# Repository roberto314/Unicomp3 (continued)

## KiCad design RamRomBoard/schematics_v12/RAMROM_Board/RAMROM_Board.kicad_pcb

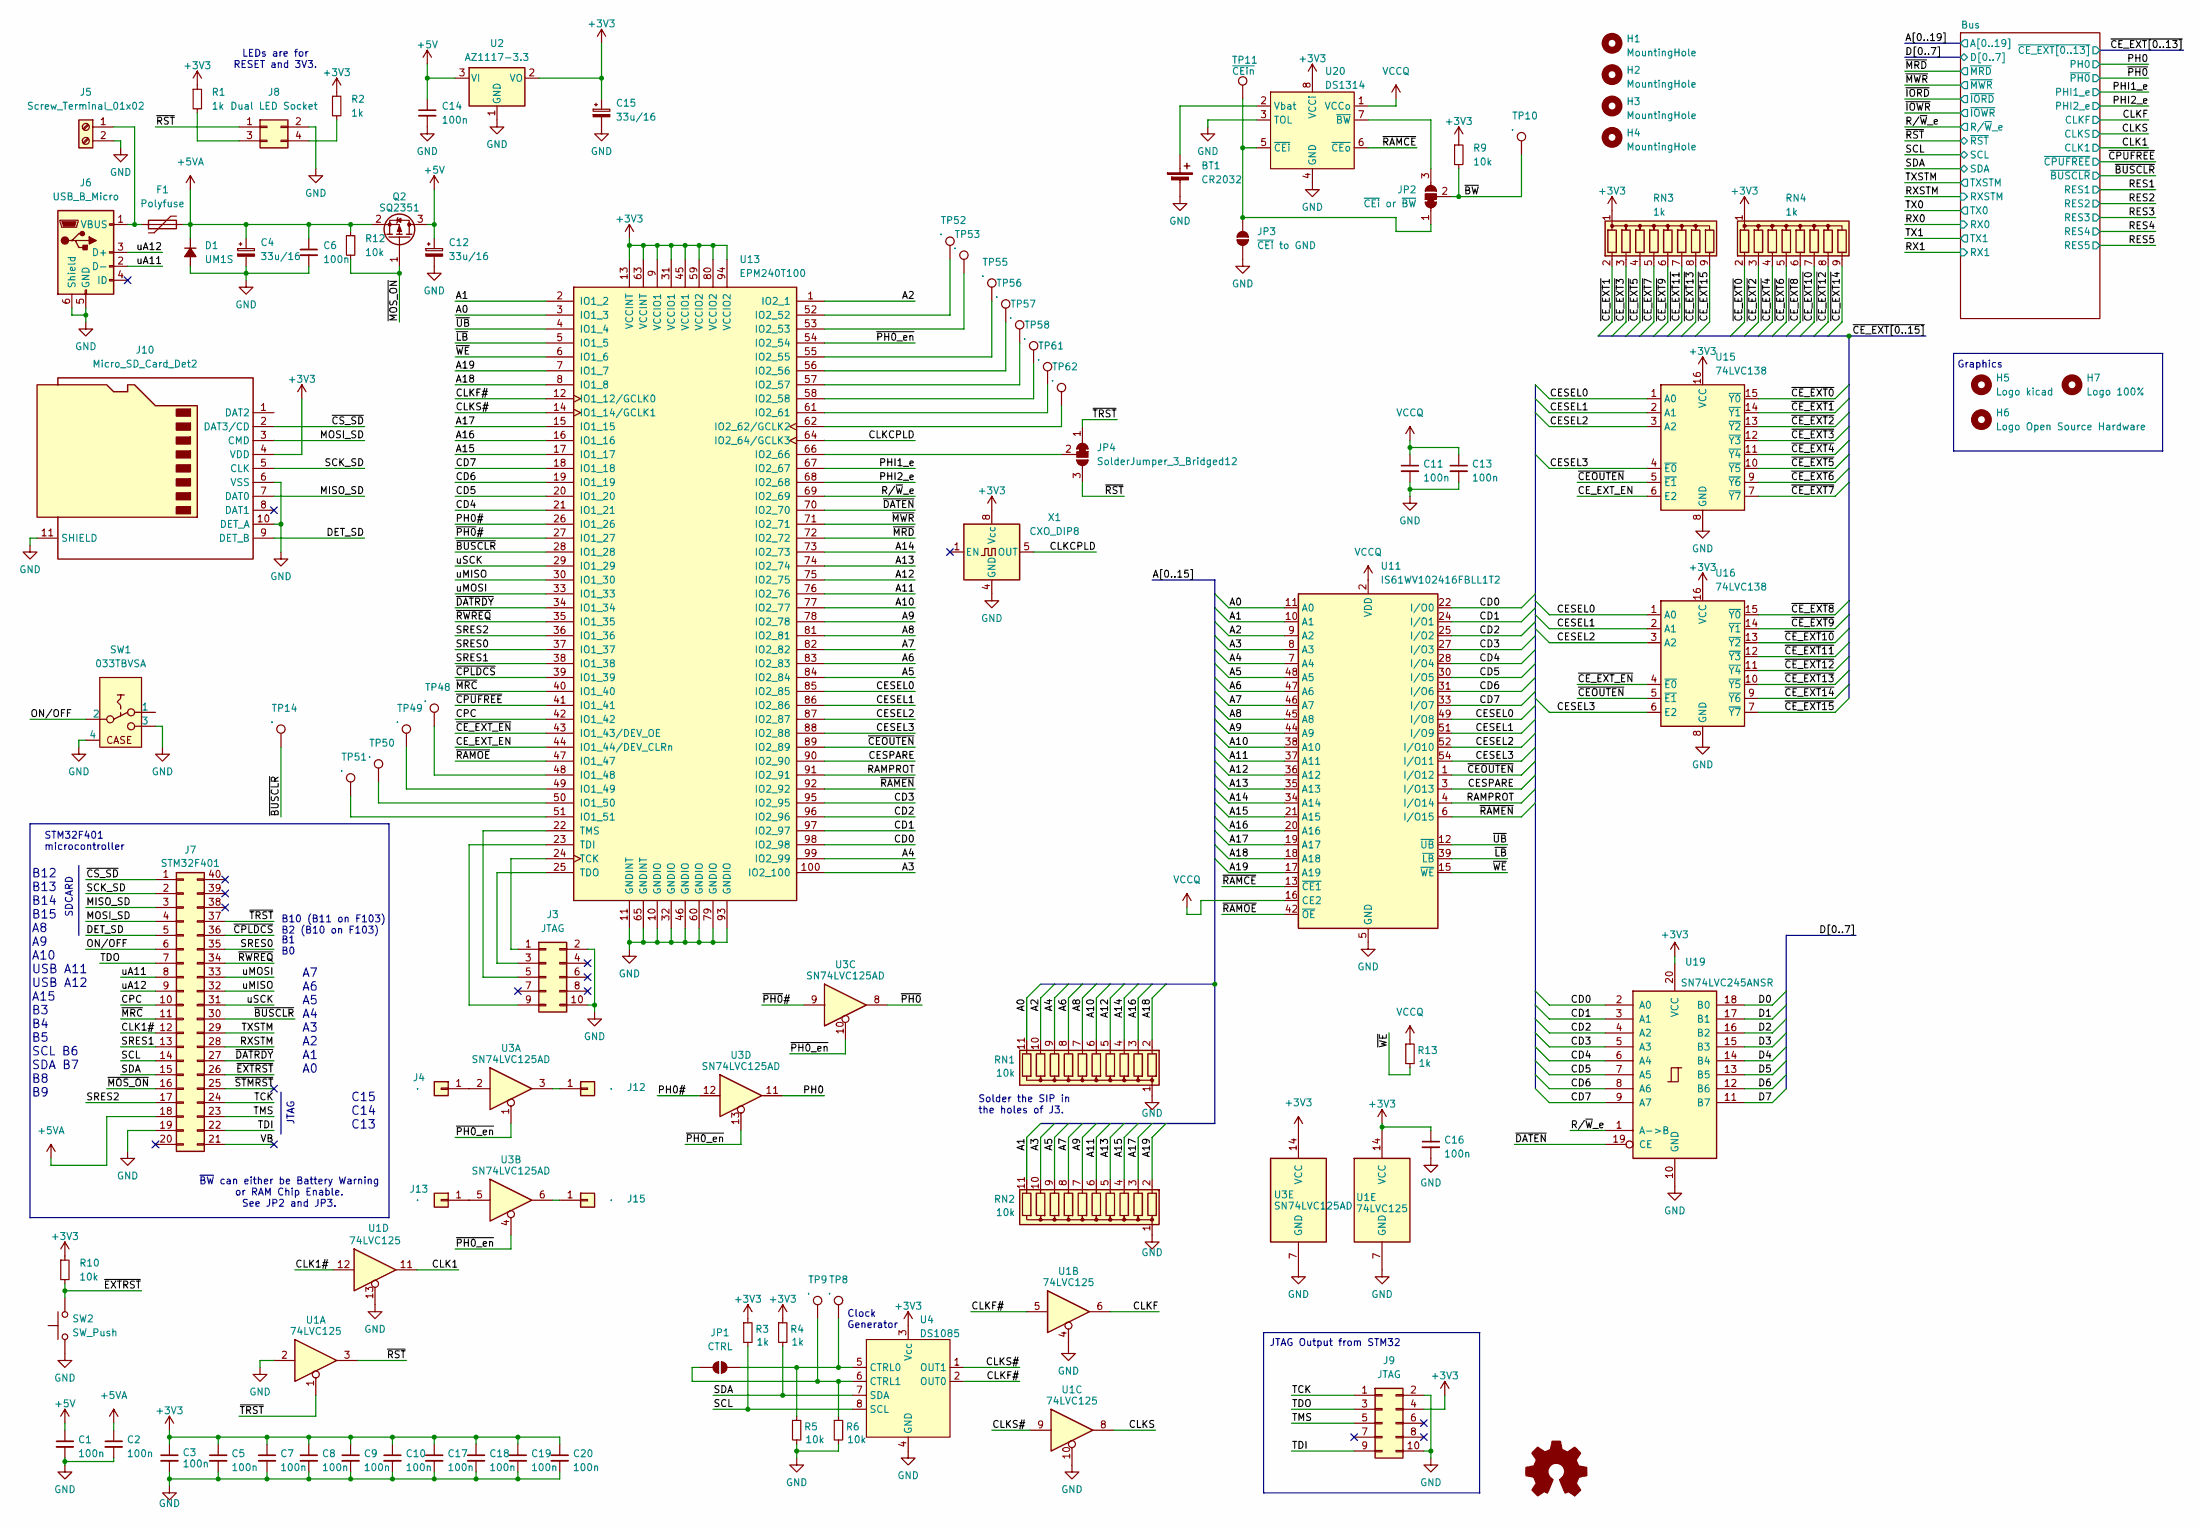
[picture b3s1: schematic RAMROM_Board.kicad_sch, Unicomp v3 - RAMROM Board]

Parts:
BT1: CR2032; Battery_CR2032_Horizontal_ThreeHoles
C1, C2, C3, C5, C6, C7, C8, C9, C10, C11, C13, C14, C16, C17, C18, C19, C20: 100n; C_1206_3216Metric
C4, C12, C15: 33u/16; CP_EIA-7343-31_Kemet-D
D1: UM1S; D_SMB
F1: Polyfuse; Fuse_Littelfuse_395Series
H1, H2, H3, H4: MountingHole; MountingHole_3.2mm_M3
H5: Logo kicad; KiCad-Logo2_6mm_SilkScreen
H6: Logo Open Source Hardware; OSHW-Logo2_7.3x6mm_SilkScreen
H7: Logo 100%; Logo_100ProzentOffner_10x2.7mm
J3: JTAG; PinHeader_2x05_P2.54mm_Vertical
J4, J12, J13, J15: .; PinHeader_1x01_P1.27mm_Vertical
J5: Screw_Terminal_01x02; TerminalBlock_RND_205-00012_1x02_P5.00mm_Horizontal
J6: USB_B_Micro; USB_Micro-B_Amphenol_10104110_Horizontal
J7: STM32F401; DIP-40_W15.24mm_Socket_LongPads
J8: Dual LED Socket; PinHeader_2x02_P2.54mm_Vertical
J9: JTAG; PinHeader_2x05_P2.54mm_Horizontal
J10: Micro_SD_Card_Det2; microSD_HC_Hirose_DM3D-SF
JP1: CTRL; SolderJumper-2_P1.3mm_Open_RoundedPad1.0x1.5mm
JP2: ~{CEi} or ~{BW}; SolderJumper-3_P1.3mm_Bridged12_RoundedPad1.0x1.5mm
JP3: ~{CEi} to GND; SolderJumper-2_P1.3mm_Open_RoundedPad1.0x1.5mm
JP4: SolderJumper_3_Bridged12; SolderJumper-3_P1.3mm_Bridged12_RoundedPad1.0x1.5mm
Q2: SQ2351; SOT-23_Handsoldering
R1, R2, R3, R4, R13: 1k; R_1206_3216Metric
R5, R6, R9, R10, R12: 10k; R_1206_3216Metric
RN1, RN2: 10k; R_Array_SIP11
RN3, RN4: 1k; R_Array_SIP9
SW1: 033TBVSA; ToggleSwitch_CTS_033TBVS
SW2: SW_Push; SW_Tactile_SPST_Angled_PTS645Vx31-2LFS
TP8, TP9, TP10, TP14, TP48, TP49, TP50, TP51, TP52, TP53, TP55, TP56, TP57, TP58, TP61, TP62: .; PinHeader_1x01_P1.00mm_Vertical
TP11: ~{CEin}; PinHeader_1x01_P1.00mm_Vertical
U1: 74LVC125; SOIC-14_3.9x8.7mm_P1.27mm
U2: AZ1117-3.3; SOT-223-3_TabPin2
U3: SN74LVC125AD; SOIC-14_3.9x8.7mm_P1.27mm
U4: DS1085; SOIC-8_3.9x4.9mm_P1.27mm
U11: IS61WV102416FBLL1T2; TSOP-II-54_22.2x10.16mm_P0.8mm
U13: EPM240T100; LQFP-100_14x14mm_P0.5mm
U15, U16: 74LVC138; SOIC-16_3.9x9.9mm_P1.27mm
U19: SN74LVC245ANSR; SO-20_5.3x12.6mm_P1.27mm
U20: DS1314; SOIC-8_3.9x4.9mm_P1.27mm
X1: CXO_DIP8; Oscillator_DIP-8

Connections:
+3V3: C3.1, C5.1, C7.1, C8.1, C9.1, C10.1, C15.1, C16.1, C17.1, C18.1, C19.1, C20.1, J9.4, J10.4 (VDD), R1.1, R2.1, R3.1, R4.1, R9.1, R10.1, RN3.1 (common), RN4.1 (common), U1.14 (VCC), U2.2 (VO), U3.14 (VCC), U4.3 (Vcc), U13.9 (VCCIO1), U13.13 (VCCINT), U13.31 (VCCIO1), U13.45 (VCCIO1), U13.59 (VCCIO2), U13.63 (VCCINT), U13.80 (VCCIO2), U13.94 (VCCIO2), U15.16 (VCC), U16.16 (VCC), U19.20 (VCC), U20.8 (VCCi), X1.8 (Vcc); also elsewhere on the board
+5V: C1.1, C12.1, C14.1, Q2.3 (D), U2.3 (VI); also elsewhere on the board
+5VA: C2.1, C4.1, C6.1, D1.1 (K), F1.2, J7.18, Q2.2 (S), R12.1; also elsewhere on the board
/A0: RN1.11 (R10), U11.11 (A0), U13.3 (IO1_3); also elsewhere on the board
/A1: RN2.11 (R10), U11.10 (A1), U13.2 (IO1_2); also elsewhere on the board
/A2: RN1.10 (R9), U11.9 (A2), U13.1 (IO2_1); also elsewhere on the board
/A3: RN2.10 (R9), U11.8 (A3), U13.100 (IO2_100); also elsewhere on the board
/A4: RN1.9 (R8), U11.7 (A4), U13.99 (IO2_99); also elsewhere on the board
/A5: RN2.9 (R8), U11.48 (A5), U13.84 (IO2_84); also elsewhere on the board
/A6: RN1.8 (R7), U11.47 (A6), U13.83 (IO2_83); also elsewhere on the board
/A7: RN2.8 (R7), U11.46 (A7), U13.82 (IO2_82); also elsewhere on the board
/A8: RN1.7 (R6), U11.45 (A8), U13.81 (IO2_81); also elsewhere on the board
/A9: RN2.7 (R6), U11.44 (A9), U13.78 (IO2_78); also elsewhere on the board
/A10: RN1.6 (R5), U11.38 (A10), U13.77 (IO2_77); also elsewhere on the board
/A11: RN2.6 (R5), U11.37 (A11), U13.76 (IO2_76); also elsewhere on the board
/A12: RN1.5 (R4), U11.36 (A12), U13.75 (IO2_75); also elsewhere on the board
/A13: RN2.5 (R4), U11.35 (A13), U13.74 (IO2_74); also elsewhere on the board
/A14: RN1.4 (R3), U11.34 (A14), U13.73 (IO2_73); also elsewhere on the board
/A15: RN2.4 (R3), U11.21 (A15), U13.17 (IO1_17); also elsewhere on the board
/A16: RN1.3 (R2), U11.20 (A16), U13.16 (IO1_16); also elsewhere on the board
/A17: RN2.3 (R2), U11.19 (A17), U13.15 (IO1_15); also elsewhere on the board
/A18: RN1.2 (R1), U11.18 (A18), U13.8 (IO1_8); also elsewhere on the board
/A19: RN2.2 (R1), U11.17 (A19), U13.7 (IO1_7); also elsewhere on the board
/CD0: U11.22 (I/O0), U13.98 (IO2_98), U19.2 (A0)
/CD1: U11.24 (I/O1), U13.97 (IO2_97), U19.3 (A1)
/CD2: U11.25 (I/O2), U13.96 (IO2_96), U19.4 (A2)
/CD3: U11.27 (I/O3), U13.95 (IO2_95), U19.5 (A3)
/CD4: U11.28 (I/O4), U13.21 (IO1_21), U19.6 (A4)
/CD5: U11.30 (I/O5), U13.20 (IO1_20), U19.7 (A5)
/CD6: U11.31 (I/O6), U13.19 (IO1_19), U19.8 (A6)
/CD7: U11.33 (I/O7), U13.18 (IO1_18), U19.9 (A7)
/CESEL0: U11.49 (I/O8), U13.85 (IO2_85), U15.1 (A0), U16.1 (A0)
/CESEL1: U11.51 (I/O9), U13.86 (IO2_86), U15.2 (A1), U16.2 (A1)
/CESEL2: U11.52 (I/O10), U13.87 (IO2_87), U15.3 (A2), U16.3 (A2)
/CESEL3: U11.54 (I/O11), U13.88 (IO2_88), U15.4 (~E0), U16.6 (E2)
/CESPARE: U11.3 (I/O13), U13.90 (IO2_90)
/CE_EXT_EN: U13.44 (IO1_44/DEV_CLRn), U15.6 (E2)
/CLK1: U1.11; also elsewhere on the board
/CLK1#: J7.12, U1.12
/CLKCPLD: U13.64 (IO2_64/GCLK3), X1.5 (OUT)
/CLKF: U1.6; also elsewhere on the board
/CLKF#: U1.5, U4.2 (OUT0), U13.12 (IO1_12/GCLK0)
/CLKS: U1.8; also elsewhere on the board
/CLKS#: U1.9, U4.1 (OUT1), U13.14 (IO1_14/GCLK1)
/CPC: J7.10, U13.42 (IO1_42)
/D0: U19.18 (B0); also elsewhere on the board
/D1: U19.17 (B1); also elsewhere on the board
/D2: U19.16 (B2); also elsewhere on the board
/D3: U19.15 (B3); also elsewhere on the board
/D4: U19.14 (B4); also elsewhere on the board
/D5: U19.13 (B5); also elsewhere on the board
/D6: U19.12 (B6); also elsewhere on the board
/D7: U19.11 (B7); also elsewhere on the board
/DET_SD: J7.5, J10.9 (DET_B)
/MISO_SD: J7.3, J10.7 (DAT0)
/MOSI_SD: J7.4, J10.3 (CMD)
/ON/OFF: J7.6, SW1.2
/PH0: U3.11; also elsewhere on the board
/PH0#: U3.12, U13.26 (IO1_26)
/PHI1_e: U13.67 (IO2_67); also elsewhere on the board
/PHI2_e: U13.68 (IO2_68); also elsewhere on the board
/RAMPROT: U11.4 (I/O14), U13.91 (IO2_91)
/RXSTM: J7.28; also elsewhere on the board
/R/~W_e: U13.69 (IO2_69), U19.1 (A->B); also elsewhere on the board
/SCK_SD: J7.2, J10.5 (CLK)
/SCL: J7.14, R3.2, U4.8 (SCL); also elsewhere on the board
/SDA: J7.15, R4.2, U4.7 (SDA); also elsewhere on the board
/SRES0: J7.35, U13.37 (IO1_37)
/SRES1: J7.13, U13.38 (IO1_38)
/SRES2: J7.17, U13.36 (IO1_36)
/TCK: J7.24, J9.1
/TDI: J7.22, J9.9
/TDO: J7.7, J9.3
/TMS: J7.23, J9.5
/TXSTM: J7.29; also elsewhere on the board
/VB: J7.21
/uA11: J6.2 (D-), J7.8
/uA12: J6.3 (D+), J7.9
/uMISO: J7.32, U13.30 (IO1_30)
/uMOSI: J7.33, U13.33 (IO1_33)
/uSCK: J7.31, U13.29 (IO1_29)
/~BUSCLR: J7.30, TP14.1, U13.28 (IO1_28); also elsewhere on the board
/~BW: JP2.2 (C), R9.2, TP10.1
/~CEOUTEN: U11.1 (I/O12), U13.89 (IO2_89), U15.5 (~E1), U16.5 (~E1)
/~CE_EXT0: RN4.2 (R1), U15.15 (~Y0); also elsewhere on the board
/~CE_EXT1: RN3.2 (R1), U15.14 (~Y1); also elsewhere on the board
/~CE_EXT2: RN4.3 (R2), U15.13 (~Y2); also elsewhere on the board
/~CE_EXT3: RN3.3 (R2), U15.12 (~Y3); also elsewhere on the board
/~CE_EXT4: RN4.4 (R3), U15.11 (~Y4); also elsewhere on the board
/~CE_EXT5: RN3.4 (R3), U15.10 (~Y5); also elsewhere on the board
/~CE_EXT6: RN4.5 (R4), U15.9 (~Y6); also elsewhere on the board
/~CE_EXT7: RN3.5 (R4), U15.7 (~Y7); also elsewhere on the board
/~CE_EXT8: RN4.6 (R5), U16.15 (~Y0); also elsewhere on the board
/~CE_EXT9: RN3.6 (R5), U16.14 (~Y1); also elsewhere on the board
/~CE_EXT10: RN4.7 (R6), U16.13 (~Y2); also elsewhere on the board
/~CE_EXT11: RN3.7 (R6), U16.12 (~Y3); also elsewhere on the board
/~CE_EXT12: RN4.8 (R7), U16.11 (~Y4); also elsewhere on the board
/~CE_EXT13: RN3.8 (R7), U16.10 (~Y5); also elsewhere on the board
/~CE_EXT14: RN4.9 (R8), U16.9 (~Y6)
/~CE_EXT15: RN3.9 (R8), U16.7 (~Y7)
/~CE_EXT_EN: U13.43 (IO1_43/DEV_OE), U16.4 (~E0)
/~CPLDCS: J7.36, U13.39 (IO1_39)
/~CPUFREE: U13.41 (IO1_41); also elsewhere on the board
/~CS_SD: J7.1, J10.2 (DAT3/CD)
/~DATEN: U13.70 (IO2_70), U19.19 (CE)
/~DATRDY: J7.27, U13.34 (IO1_34)
/~EXTRST: J7.26, R10.2, SW2.2
/~LB: U11.39 (~LB), U13.5 (IO1_5)
/~MOS_ON: J7.16, Q2.1 (G), R12.2
/~MRC: J7.11, U13.40 (IO1_40)
/~MRD: U13.72 (IO2_72); also elsewhere on the board
/~MWR: U13.71 (IO2_71); also elsewhere on the board
/~PH0_en: U3.1, U3.4, U3.10, U3.13, U13.54 (IO2_54)
/~PH0: U3.8; also elsewhere on the board
/~PH0#: U3.9, U13.27 (IO1_27)
/~RAMCE: U11.13 (~CE1), U20.6 (~CEo)
/~RAMEN: U11.6 (I/O15), U13.92 (IO2_92)
/~RAMOE: U11.42 (~OE), U13.47 (IO1_47)
/~RST: J8.1, JP4.3 (B), U1.3; also elsewhere on the board
/~RWREQ: J7.34, U13.35 (IO1_35)
/~STMRST: J7.25
/~TRST: J7.37, JP4.1 (A), U1.1
/~UB: U11.12 (~UB), U13.4 (IO1_4)
/~WE: R13.2, U11.15 (~WE), U13.6 (IO1_6)
GND: BT1.2 (-), C1.2, C2.2, C3.2, C4.2, C5.2, C6.2, C7.2, C8.2, C9.2, C10.2, C11.2, C12.2, C13.2, C14.2, C15.2, C16.2, C17.2, C18.2, C19.2, C20.2, D1.2 (A), J3.2, J3.10, J5.2, J6.5 (GND), J6.6 (Shield), J7.19, J8.2, J9.2, J9.10, J10.6 (VSS), J10.10 (DET_A), J10.11 (SHIELD), JP3.1 (A), R5.2, R6.2, RN1.1 (common), RN2.1 (common), SW1.3, SW1.4, SW2.1, U1.2, U1.4, U1.7 (GND), U1.10, U1.13, U2.1 (GND), U3.7 (GND), U4.4 (GND), U11.5 (GND), U11.26 (GND), U11.32 (GND), U11.41 (GND), U11.53 (GND), U13.10 (GNDIO), U13.11 (GNDINT), U13.32 (GNDIO), U13.46 (GNDIO), U13.60 (GNDIO), U13.65 (GNDINT), U13.79 (GNDIO), U13.93 (GNDIO), U15.8 (GND), U16.8 (GND), U19.10 (GND), U20.3 (TOL), U20.4 (GND), X1.4 (GND); also elsewhere on the board
unnamed: BT1.1 (+), U20.2 (Vbat)
unnamed: J3.1, U13.24 (TCK)
unnamed: J3.3, U13.25 (TDO)
unnamed: J3.5, U13.22 (TMS)
unnamed: J3.9, U13.23 (TDI)
unnamed: J4.1, U3.2
unnamed: F1.1, J5.1, J6.1 (VBUS)
unnamed: J8.3, R1.2
unnamed: J8.4, R2.2
unnamed: J12.1, U3.3
unnamed: J13.1, U3.5
unnamed: J15.1, U3.6
unnamed: JP1.1 (A), R5.1, TP8.1, U4.5 (CTRL0)
unnamed: JP1.2 (B), R6.1, TP9.1, U4.6 (CTRL1)
unnamed: JP2.1 (A), JP3.2 (B), TP11.1, U20.5 (~CEi)
unnamed: JP2.3 (B), U20.7 (~BW)
unnamed: JP4.2 (C), U13.66 (IO2_66)
unnamed: TP48.1, U13.48 (IO1_48)
unnamed: TP49.1, U13.49 (IO1_49)
unnamed: TP50.1, U13.50 (IO1_50)
unnamed: TP51.1, U13.51 (IO1_51)
unnamed: TP52.1, U13.52 (IO2_52)
unnamed: TP53.1, U13.53 (IO2_53)
unnamed: TP55.1, U13.55 (IO2_55)
unnamed: TP56.1, U13.56 (IO2_56)
unnamed: TP57.1, U13.57 (IO2_57)
unnamed: TP58.1, U13.58 (IO2_58)
unnamed: TP61.1, U13.61 (IO2_61)
unnamed: TP62.1, U13.62 (IO2_62/GCLK2)
VCCQ: C11.1, C13.1, R13.1, U11.2 (VDD), U11.14 (VDD), U11.16 (CE2), U11.23 (VDD), U11.29 (VDD), U11.50 (VDD), U20.1 (VCCo)

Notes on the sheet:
JTAG Output from STM32
SDCARD
B1 B0
JTAG
Graphics
LEDs are for RESET and 3V3.
~{BW} can either be Battery Warning or RAM Chip Enable. See JP2 and JP3.
B10 (B11 on F103) B2 (B10 on F103)
A7 A6 A5 A4 A3 A2 A1 A0
Clock Generator
Solder the SIP in the holes of J3.
B12 B13 B14 B15 A8 A9 A10 USB A11 USB A12 A15 B3 B4 B5 SCL B6 SDA B7 B8 B9
C15 C14 C13
STM32F401 microcontroller

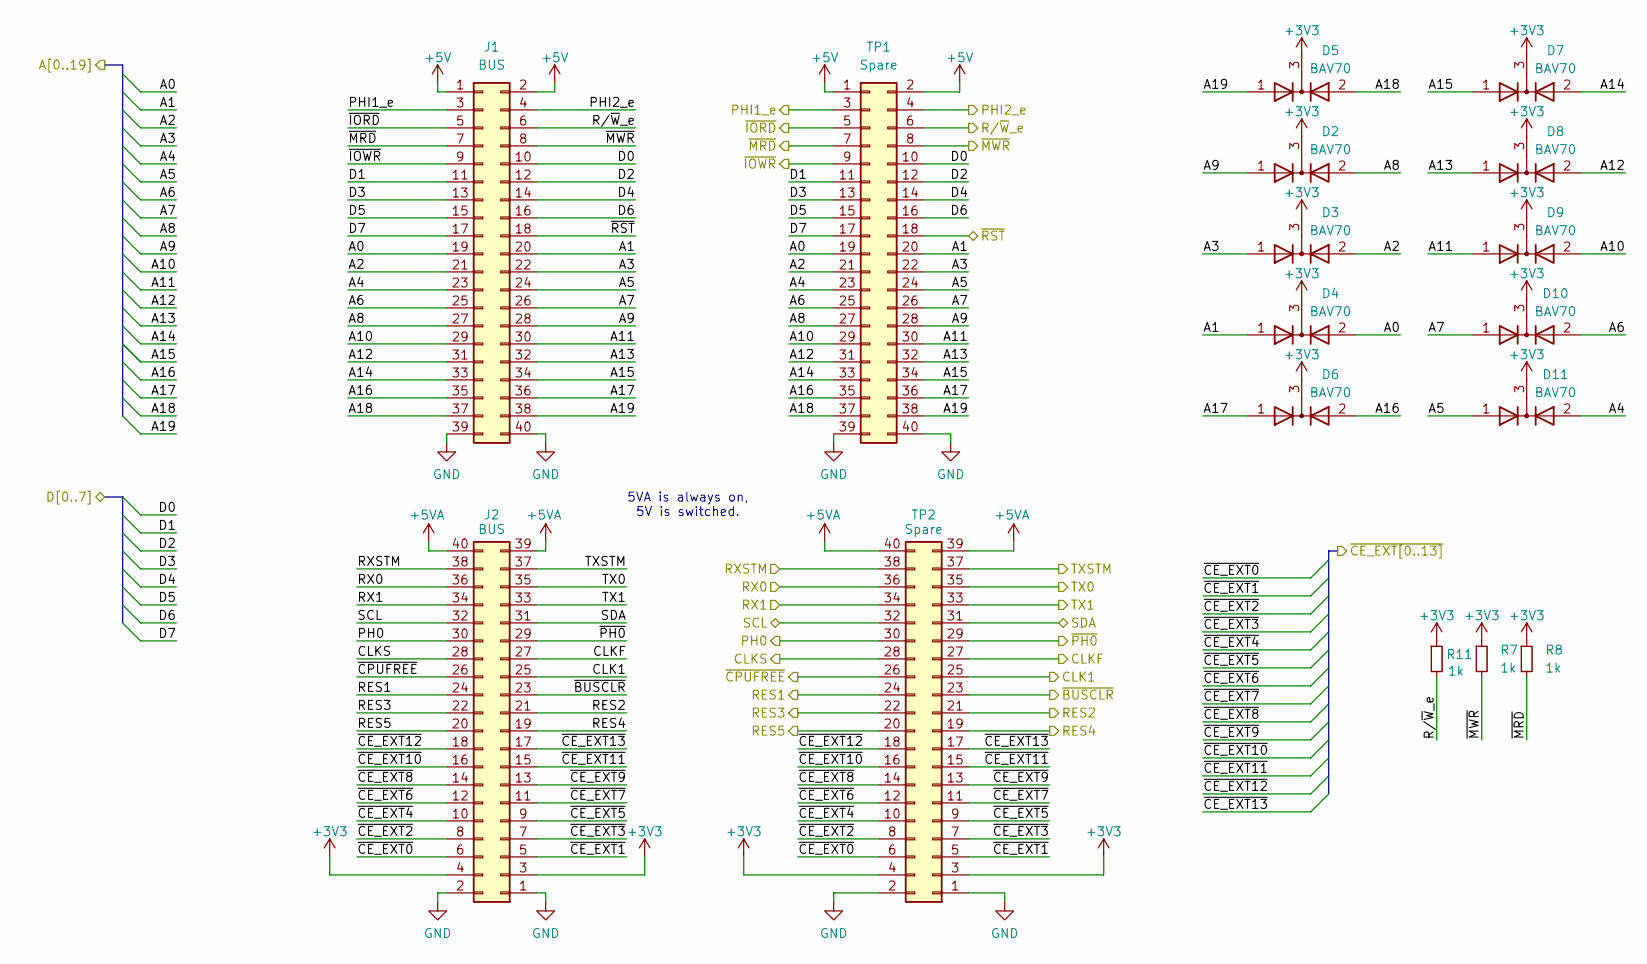
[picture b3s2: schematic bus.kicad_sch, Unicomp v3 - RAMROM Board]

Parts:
D2, D3, D4, D5, D6, D7, D8, D9, D10, D11: BAV70; SOT-23
J1, J2: BUS; PinSocket_2x20_P2.54mm_Vertical
R7, R8, R11: 1k; R_1206_3216Metric
TP1, TP2: Spare; PinSocket_2x20_P2.54mm_Vertical

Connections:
+3V3: D2.3 (K), D3.3 (K), D4.3 (K), D5.3 (K), D6.3 (K), D7.3 (K), D8.3 (K), D9.3 (K), D10.3 (K), D11.3 (K), J2.3, J2.4, R7.1, R8.1, R11.1, TP2.3, TP2.4; also elsewhere on the board
+5V: J1.1, J1.2, TP1.1, TP1.2; also elsewhere on the board
+5VA: J2.39, J2.40, TP2.39, TP2.40; also elsewhere on the board
/A0: D4.2 (A), J1.19, TP1.19; also elsewhere on the board
/A1: D4.1 (A), J1.20, TP1.20; also elsewhere on the board
/A2: D3.2 (A), J1.21, TP1.21; also elsewhere on the board
/A3: D3.1 (A), J1.22, TP1.22; also elsewhere on the board
/A4: D11.2 (A), J1.23, TP1.23; also elsewhere on the board
/A5: D11.1 (A), J1.24, TP1.24; also elsewhere on the board
/A6: D10.2 (A), J1.25, TP1.25; also elsewhere on the board
/A7: D10.1 (A), J1.26, TP1.26; also elsewhere on the board
/A8: D2.2 (A), J1.27, TP1.27; also elsewhere on the board
/A9: D2.1 (A), J1.28, TP1.28; also elsewhere on the board
/A10: D9.2 (A), J1.29, TP1.29; also elsewhere on the board
/A11: D9.1 (A), J1.30, TP1.30; also elsewhere on the board
/A12: D8.2 (A), J1.31, TP1.31; also elsewhere on the board
/A13: D8.1 (A), J1.32, TP1.32; also elsewhere on the board
/A14: D7.2 (A), J1.33, TP1.33; also elsewhere on the board
/A15: D7.1 (A), J1.34, TP1.34; also elsewhere on the board
/A16: D6.2 (A), J1.35, TP1.35; also elsewhere on the board
/A17: D6.1 (A), J1.36, TP1.36; also elsewhere on the board
/A18: D5.2 (A), J1.37, TP1.37; also elsewhere on the board
/A19: D5.1 (A), J1.38, TP1.38; also elsewhere on the board
/CLK1: J2.25, TP2.25; also elsewhere on the board
/CLKF: J2.27, TP2.27; also elsewhere on the board
/CLKS: J2.28, TP2.28; also elsewhere on the board
/D0: J1.10, TP1.10; also elsewhere on the board
/D1: J1.11, TP1.11; also elsewhere on the board
/D2: J1.12, TP1.12; also elsewhere on the board
/D3: J1.13, TP1.13; also elsewhere on the board
/D4: J1.14, TP1.14; also elsewhere on the board
/D5: J1.15, TP1.15; also elsewhere on the board
/D6: J1.16, TP1.16; also elsewhere on the board
/D7: J1.17, TP1.17; also elsewhere on the board
/PH0: J2.30, TP2.30; also elsewhere on the board
/PHI1_e: J1.3, TP1.3; also elsewhere on the board
/PHI2_e: J1.4, TP1.4; also elsewhere on the board
/RES1: J2.24, TP2.24
/RES2: J2.21, TP2.21
/RES3: J2.22, TP2.22
/RES4: J2.19, TP2.19
/RES5: J2.20, TP2.20
/RX0: J2.36, TP2.36
/RX1: J2.34, TP2.34
/RXSTM: J2.38, TP2.38; also elsewhere on the board
/R/~W_e: J1.6, R11.2, TP1.6; also elsewhere on the board
/SCL: J2.32, TP2.32; also elsewhere on the board
/SDA: J2.31, TP2.31; also elsewhere on the board
/TX0: J2.35, TP2.35
/TX1: J2.33, TP2.33
/TXSTM: J2.37, TP2.37; also elsewhere on the board
/~BUSCLR: J2.23, TP2.23; also elsewhere on the board
/~CE_EXT0: J2.6, TP2.6; also elsewhere on the board
/~CE_EXT1: J2.5, TP2.5; also elsewhere on the board
/~CE_EXT2: J2.8, TP2.8; also elsewhere on the board
/~CE_EXT3: J2.7, TP2.7; also elsewhere on the board
/~CE_EXT4: J2.10, TP2.10; also elsewhere on the board
/~CE_EXT5: J2.9, TP2.9; also elsewhere on the board
/~CE_EXT6: J2.12, TP2.12; also elsewhere on the board
/~CE_EXT7: J2.11, TP2.11; also elsewhere on the board
/~CE_EXT8: J2.14, TP2.14; also elsewhere on the board
/~CE_EXT9: J2.13, TP2.13; also elsewhere on the board
/~CE_EXT10: J2.16, TP2.16; also elsewhere on the board
/~CE_EXT11: J2.15, TP2.15; also elsewhere on the board
/~CE_EXT12: J2.18, TP2.18; also elsewhere on the board
/~CE_EXT13: J2.17, TP2.17; also elsewhere on the board
/~CPUFREE: J2.26, TP2.26; also elsewhere on the board
/~IORD: J1.5, TP1.5
/~IOWR: J1.9, TP1.9
/~MRD: J1.7, R8.2, TP1.7; also elsewhere on the board
/~MWR: J1.8, R7.2, TP1.8; also elsewhere on the board
/~PH0: J2.29, TP2.29; also elsewhere on the board
/~RST: J1.18, TP1.18; also elsewhere on the board
GND: J1.39, J1.40, J2.1, J2.2, TP1.39, TP1.40, TP2.1, TP2.2; also elsewhere on the board

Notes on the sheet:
5VA is always on, 5V is switched.

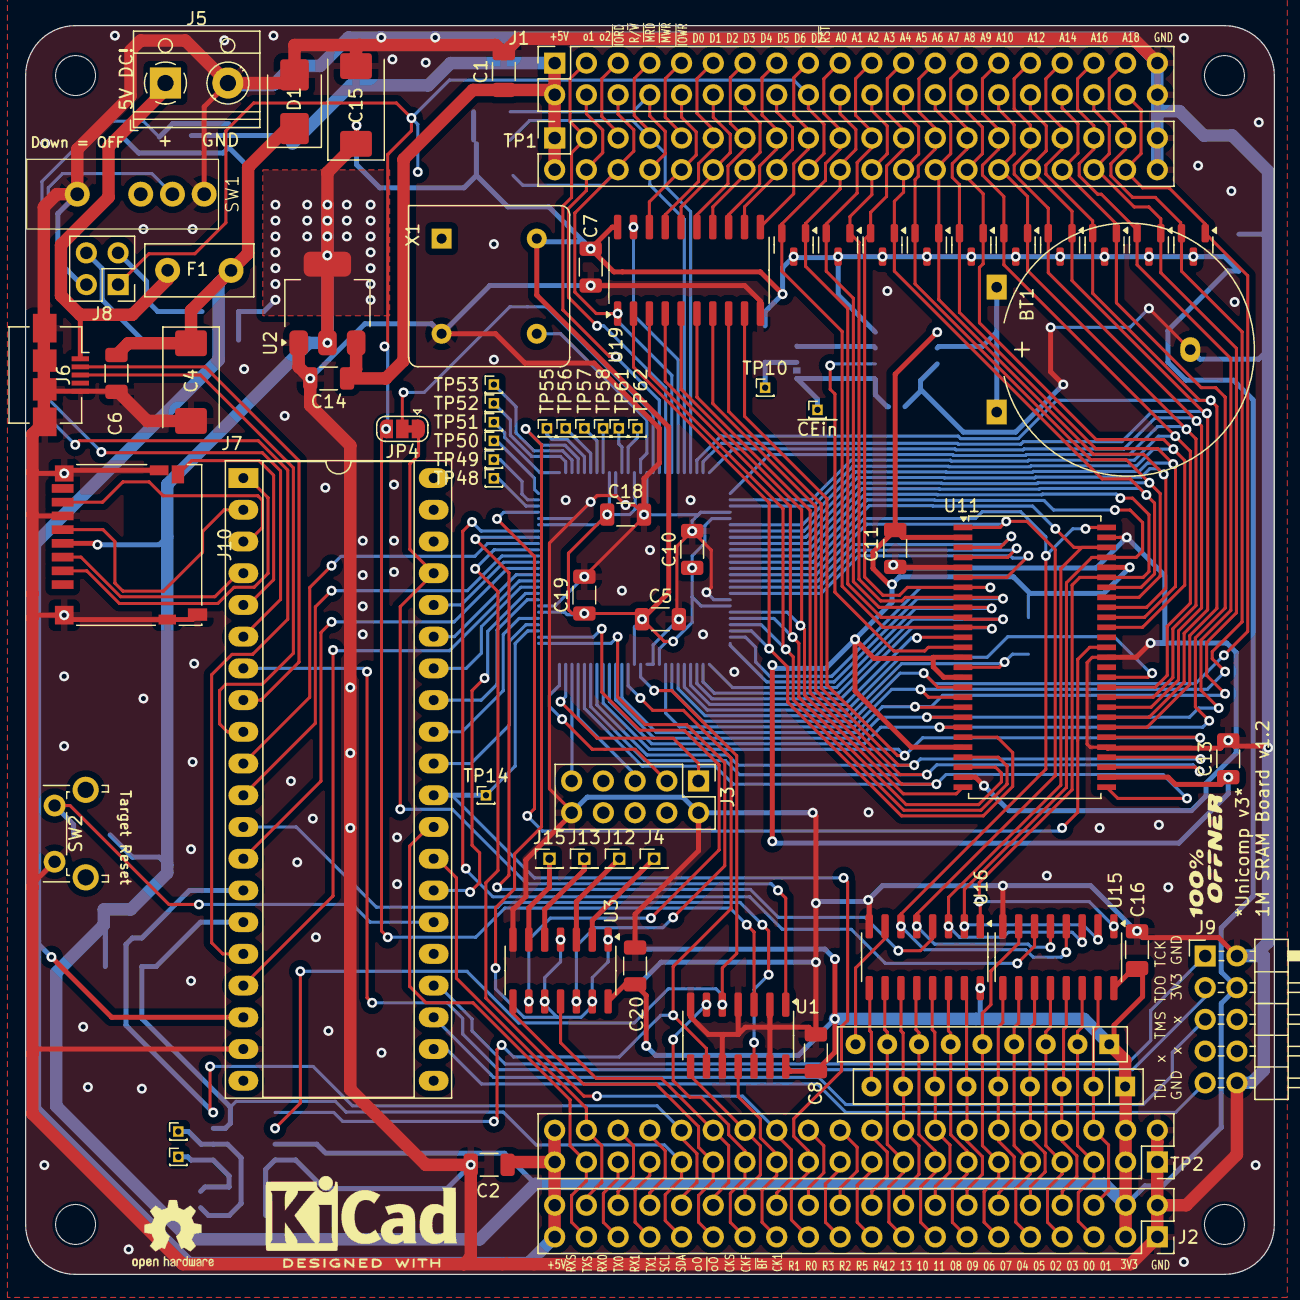
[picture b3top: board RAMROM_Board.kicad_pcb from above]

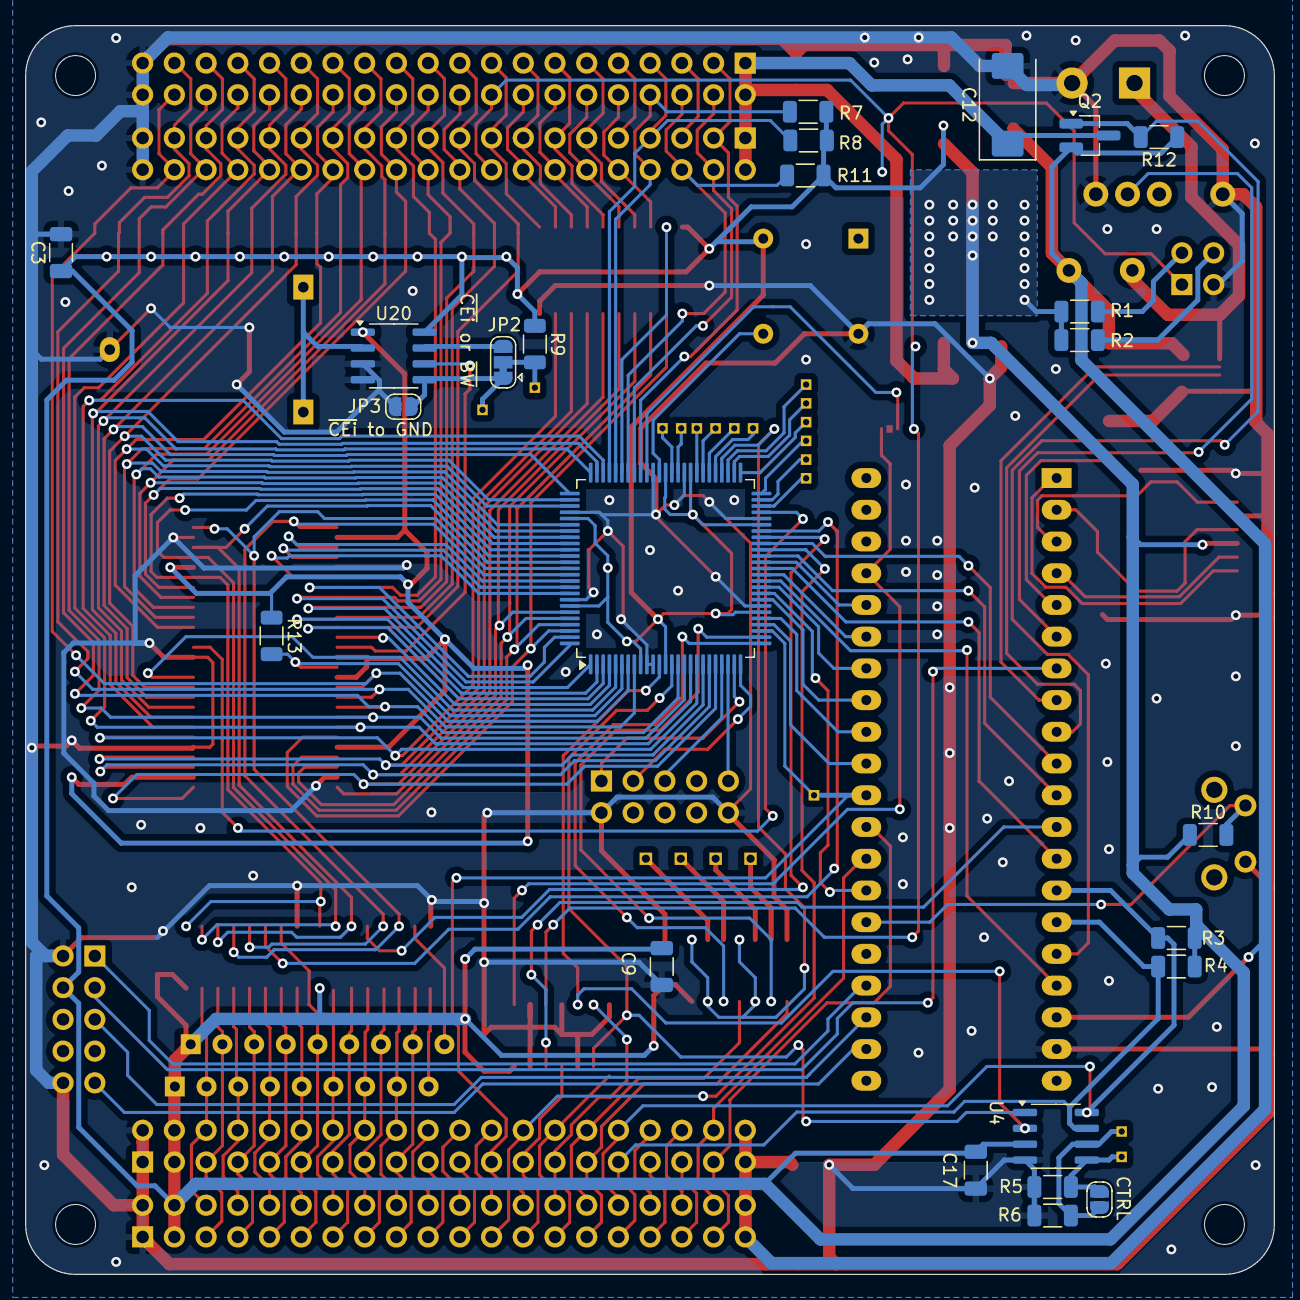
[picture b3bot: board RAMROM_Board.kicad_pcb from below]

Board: 2 copper layers, 100.0 x 100.0 mm, 105 parts (24 on the bottom side), 164 nets.
